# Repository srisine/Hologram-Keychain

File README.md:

# Hologram-Keychain

<h1>Description</h1>
This was a project that I wanted to build for a long time as its just so cool. It's a tabletop/keychain like device that displays stuff as holograms. It uses an I2C OLED display to show content and then with the help of a cubical prism converts it into a holographic display. It uses concepts of physics like refraction and internal reflection to achieve this. And the best part it just looks so cool!

<h1>Why I Made This</h1>
One day while scrolling on youtube I came across a video where they uses this technology to display lyrics of a song and I was fascinated I wanted to build it then and there but due to some stuff I couldn't but now that I've got the opportunity to build it I'm building it. Being a cse/physics enthusiast I've always wanted something that uses both subjects and looks cool and this is the most perfect project for this! Also I wanna impress my friends who bully me ;)...

<h1>Project Images</h1>

<h1>PCB/Wiring</h1>
Designed in KiCAD!

# BOM

| Component | Qty | Source | Price (USD) | Link |
| :--- | :---: | :---: | :---: | :---: |
| Seeed Studio XIAO ESP32-C3 | 1 | Online | $8.71 | [Robu.in](https://robu.in/product/seeed-studio-xiao-esp32c3-tiny-mcu-board-with-wi-fi-and-ble-battery-charge-supported-power-efficiency-and-rich-interface/) |
| 0.96-inch I2C OLED Display | 1 | Online | $3.50 | [Robu.in](https://robu.in/product/0-96-inch-i2c-iic-oled-lcd-module-4pin-with-vcc-gnd-white/) |
| Beam Splitter Cube (20x20x20mm) | 1 | Online | $35.99 | [Amazon](https://www.amazon.in/gp/product/B0F7KBNGXD/ref=ox_sc_act_title_1?smid=A103TM47B6U43L&psc=1) |
| Custom PCB Board | 1 | Online | $29.00 | [JLCPCB](https://jlcpcb.com) |
| 3D Printed Case | 1 set | Online | $2.00 | Robu.in |
| M3 Screws & Standoffs Assortment | 1 set | Local | ~$2.00 | Local Market |
| **Subtotal (Online Purchases)** | **5** | **Online** | **~$79.20** | **—** |
| **Subtotal (Local Purchases)** | **1** | **Local** | **~$2.00** | **—** |
| **Grand Total** | **6 items** | **All** | **~$81.20** | **—** |

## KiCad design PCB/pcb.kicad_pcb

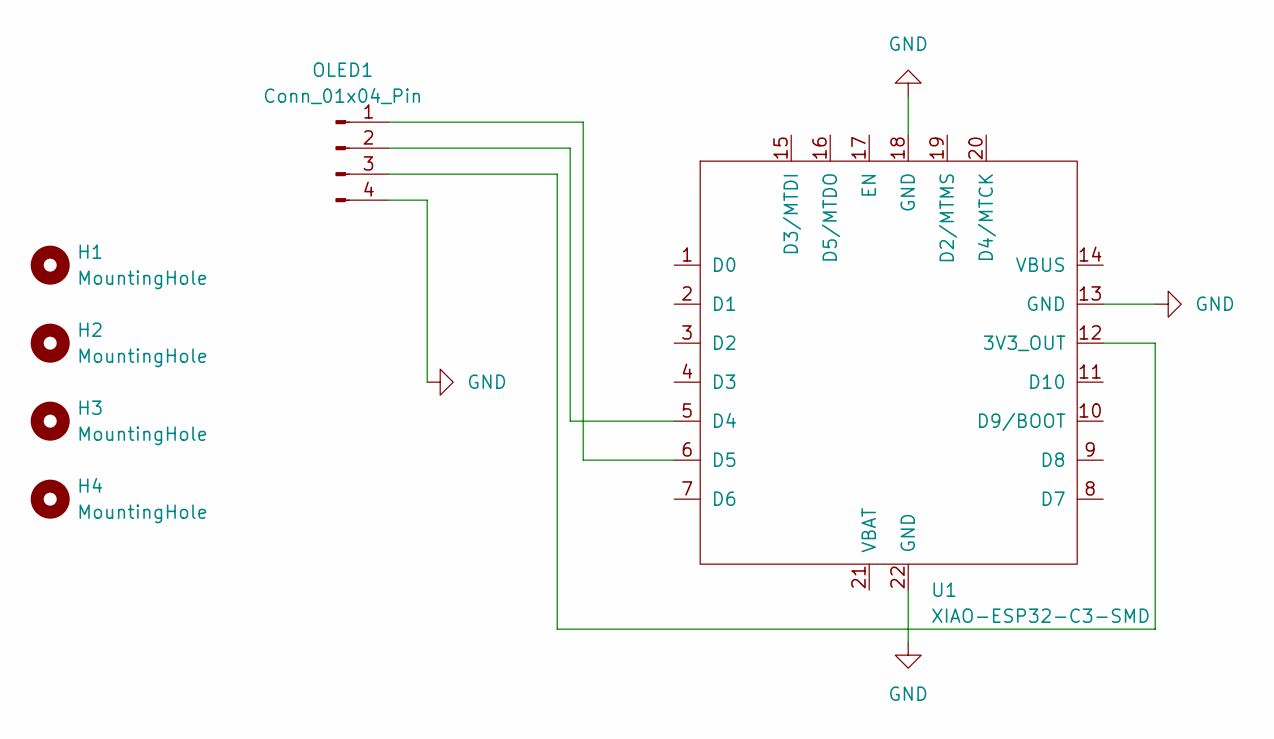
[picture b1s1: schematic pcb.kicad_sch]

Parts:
H1, H2, H3, H4: MountingHole; MountingHole_2.1mm
OLED1: Conn_01x04_Pin; PinHeader_1x04_P2.54mm_Vertical
U1: XIAO-ESP32-C3-SMD

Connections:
GND: OLED1.4, U1.13 (GND), U1.18 (GND), U1.22 (GND)
unnamed: OLED1.1, U1.6 (D5)
unnamed: OLED1.2, U1.5 (D4)
unnamed: OLED1.3, U1.12 (3V3_OUT)

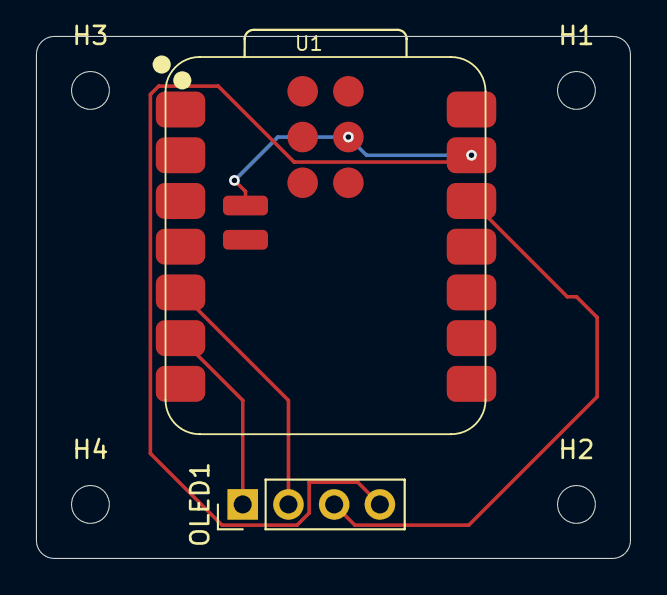
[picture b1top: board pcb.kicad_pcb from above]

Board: 2 copper layers, 33.0 x 29.0 mm, 6 parts (0 on the bottom side), 4 nets.
